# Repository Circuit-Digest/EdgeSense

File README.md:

# EdgeSense: STM32 Edge AI Texture and Gesture Classifier

```
  ███████╗██████╗  ██████╗ ███████╗███████╗███████╗███╗   ██╗███████╗███████╗
  ██╔════╝██╔══██╗██╔════╝ ██╔════╝██╔════╝██╔════╝████╗  ██║██╔════╝██╔════╝
  █████╗  ██║  ██║██║  ███╗█████╗  ███████╗█████╗  ██╔██╗ ██║███████╗█████╗  
  ██╔══╝  ██║  ██║██║   ██║██╔══╝  ╚════██║██╔══╝  ██║╚██╗██║╚════██║██╔══╝  
  ███████╗██████╔╝╚██████╔╝███████╗███████║███████╗██║ ╚████║███████║███████╗
  ╚══════╝╚═════╝  ╚═════╝ ╚══════╝╚══════╝╚══════╝╚═╝  ╚═══╝╚══════╝╚══════╝
```

**EdgeSense** is a compact, high-performance edge artificial intelligence platform that performs on-device 3D gesture recognition, surface/texture classification, static hand posture detection, and optical obscuration sensing. 

Powered by the **STM32H533CEU6** (ARM Cortex-M33 running at 250 MHz) and the **ST VL53L8CH** 8x8 direct Time-of-Flight (dToF) sensor, EdgeSense executes quantized neural networks entirely on-chip in real time with sub-7 ms inference latency.

---

## Key Capabilities

EdgeSense features a runtime multi-model execution engine (`pipeline_manager.c`) allowing dynamic model switching over USB CDC:

1. **3D Gesture Recognition (8x8 ToF, 15 FPS)**:
   - Recognizes dynamic directional swipes: `SWIPE_LEFT`, `SWIPE_RIGHT`, `SWIPE_UP`, `SWIPE_DOWN`, and `IDLE`.
   - Continuous 15-frame sliding window (1.0 s temporal context) with zero gesture-lockout.
   - Physical temporal motion energy guard to eliminate stationary phantom triggers.
   - Inference latency: **~6.8 ms** per inference.

2. **Distance-Invariant Surface Classifier (4x4 CNH, 48 Bins)**:
   - Classifies textures and materials: `HARD_FLOOR` (tile/wood), `CARPET` (subsurface scattering), `SPECULAR` (mirrors/polished metal), and `VOID` (drop-offs/cliffs).
   - Utilizes ST-aligned Cumulative Normalized Histogram (CNH) peak-centered canonical alignment.
   - Inference latency: **~3.2 ms** per inference.

3. **Static Hand Posture Classifier (8x8 Depth + Signal Intensity)**:
   - Identifies static human hand postures: `FLAT_HAND`, `LIKE`, `DISLIKE`, `BREAK_TIME`, `FIST`, and `NONE`.
   - Dual-channel 2D-CNN processing distance geometry and photon reflection intensity simultaneously.
   - Robust to ambient lighting variations and skin tone differences.
   - Inference latency: **~4.1 ms** per inference.

4. **Optical Obscuration & Smoke Detector**:
   - Detects microscopic particles, airborne obscuration, and smoke.
   - Computes multi-zone signal attenuation and ambient light scattering indices in real time.

---

## Hardware Specifications

| Component | Specification |
|---|---|
| **Microcontroller** | STMicroelectronics STM32H533CEUx (ARM Cortex-M33, 250 MHz, TrustZone, FPU, DSP) |
| **On-Chip Memory** | 512 KB Flash ROM, 256 KB SRAM |
| **ToF Sensor** | STMicroelectronics VL53L8CH / VL53LMZ Direct Time-of-Flight |
| **Sensor FoV** | 65° Diagonal Field of View |
| **Spatial Resolution** | 8x8 (64 zones) or 4x4 (16 zones with 48-bin CNH histograms) |
| **Ranging Distance** | 20 mm to 4000 mm |
| **Host Connectivity** | High-Speed USB 2.0 CDC (Virtual COM Port @ 921600 baud) |
| **Communication Bus** | Dedicated Fast-mode Plus (Fm+) 1 MHz I2C bus |
| **Power Supply** | 5V via USB-C or 3.3V external rail |

---

## Repository Structure

```
EdgeSense/
├── Core/                      # STM32H533 HAL drivers, ISRs, and main loop
├── Drivers/                   # CMSIS and STM32H5xx HAL libraries
├── Middlewares/               # ST X-CUBE-AI runtime v10.2.1 & USB Device stack
├── USB_Device/                # USB CDC Virtual COM Port descriptors & handlers
├── VL53LMZ_ULD/               # Ultra-Lite Driver & CNH Histogram Plugin
├── X-CUBE-AI/                 # Edge AI Pipeline Manager & Active Networks
│   └── App/                   # pipeline_manager, model_gesture, model_posture, model_surface, model_smoke
│
├── Models/                    # Pre-trained production ONNX models & datasets
│   ├── gesture_nn_model.onnx  # 5-class 2D-CNN Gesture Classifier
│   ├── posture_nn_model.onnx  # 6-class 2D-CNN Posture Classifier
│   ├── surface_nn_model.onnx  # 4-class 1D-CNN Surface Classifier
│   ├── gesture_dataset.npz    # Default Gesture training dataset
│   ├── posture_dataset.npz    # Default Posture training dataset
│   ├── surface_dataset.npz    # Default Surface training dataset
│   └── Archive/               # Intermediate training iterations
│
├── Tools/                     # Python Studio, GUIs, and deploy automation
│   ├── Studio/                # 4-in-1 EdgeSense Neural Network Studio
│   │   ├── run_nn_studio.bat  # Double-click to launch Studio GUI
│   │   ├── deploy_to_project.bat # Unified model conversion & firmware build
│   │   ├── edgesense_nn_studio.py
│   │   ├── requirements.txt
│   │   └── utils/             # ST-AI helpers and zip importers
│   ├── Visualizer/            # Real-time multi-zone depth viewer
│   ├── Flashing/              # STM32CubeProgrammer CLI flasher (USB DFU & ST-LINK)
│   └── Tests/                 # Automated AT pipeline verification tests
│
├── Hardware/                  # KiCad EDA design files, schematics & BOM
│   ├── Schematics/            # KiCad project, schematics, PCB layout
│   └── Production/            # Gerber ZIP, Pick-and-Place, BOM
│
├── Docs/                      # Technical references & protocol manuals
│   ├── Architecture.md        # System architecture and memory specs
│   └── AT_Command_Manual.md   # Complete AT command serial reference
│
├── EdgeSense.ioc              # STM32CubeMX hardware pinout and clock config
├── STM32H533CEUX_FLASH.ld     # Flash linker script
├── LICENSE                    # GNU General Public License v3.0
└── README.md                  # This documentation
```

---

## Getting Started

### 1. Prerequisites
- **STM32CubeIDE** (v2.2.0 or newer) with GNU Tools for STM32 (ARM GCC 14.3+)
- **STM32Cube.AI Studio (STEDGEAI-CUBEAI)** / **ST Edge AI Core** (`stedgeai`) v10.2.1+
- **Python** 3.10+ (64-bit)
- **ST-LINK V2 / V3** Programmer

### 2. Python Environment Setup
Install the required dependencies for the EdgeSense AI Studio:
```bash
cd Tools/Studio
pip install -r requirements.txt
```

### 3. Launching EdgeSense Studio
Double-click `Tools/Studio/run_nn_studio.bat` or run:
```bash
python Tools/Studio/edgesense_nn_studio.py
```
From the Studio, you can:
- View live 8x8 depth heatmaps and 4x4 CNH pulse shapes.
- Record new training datasets for Gestures, Postures, or Surfaces.
- Train PyTorch neural networks with 1 click.
- Deploy trained models to the project via `deploy_to_project.bat`.

### 4. Building Firmware via Command Line
```bash
make -C Debug all
```
The compiled binary will be located at `Debug/EdgeSense.elf` and `Debug/EdgeSense.bin`.

### 5. Flashing Firmware
Choose your preferred flashing method:
- **USB-C (DFU Mode - No external programmer required)**:
  1. Press and hold `SW2` (BOOT0), press and release `SW1` (RESET), then release `SW2`.
  2. Run:
  ```bash
  Tools/Flashing/flash_firmware_usb.bat
  ```
- **ST-LINK (SWD Mode)**:
  Connect your ST-LINK probe to the J3 header and run:
  ```bash
  Tools/Flashing/flash_firmware.bat
  ```
- **STM32CubeIDE**:
  Open the project in STM32CubeIDE and click **Run** or **Debug**.

---

## Serial Communication & AT Commands

Connect to the USB CDC COM port at **921600 baud, 8-N-1**.

| Command | Action |
|---|---|
| `AT` | Verify connection (returns `OK`) |
| `AT+MODE=?` | List available modes: `(0:GESTURE, 1:SURFACE, 2:POSTURE, 3:SMOKE)` |
| `AT+MODE?` | Query currently active mode |
| `AT+MODE=0` | Switch to 3D Gesture Recognition mode |
| `AT+MODE=1` | Switch to Surface / Texture Classifier mode |
| `AT+MODE=2` | Switch to Hand Posture Classifier mode |
| `AT+MODE=3` | Switch to Optical Smoke / Obscuration mode |
| `AT+STREAM=1` | Enable real-time 8x8 JSON depth streaming |
| `AT+STREAM=0` | Disable streaming |
| `AT+STATUS` | View sensor health, frame counts, and FPS |
| `AT+RESET` | Software system reboot |

---

## License

This project is licensed under the **GNU General Public License v3.0**. See the [LICENSE](LICENSE) file for details.

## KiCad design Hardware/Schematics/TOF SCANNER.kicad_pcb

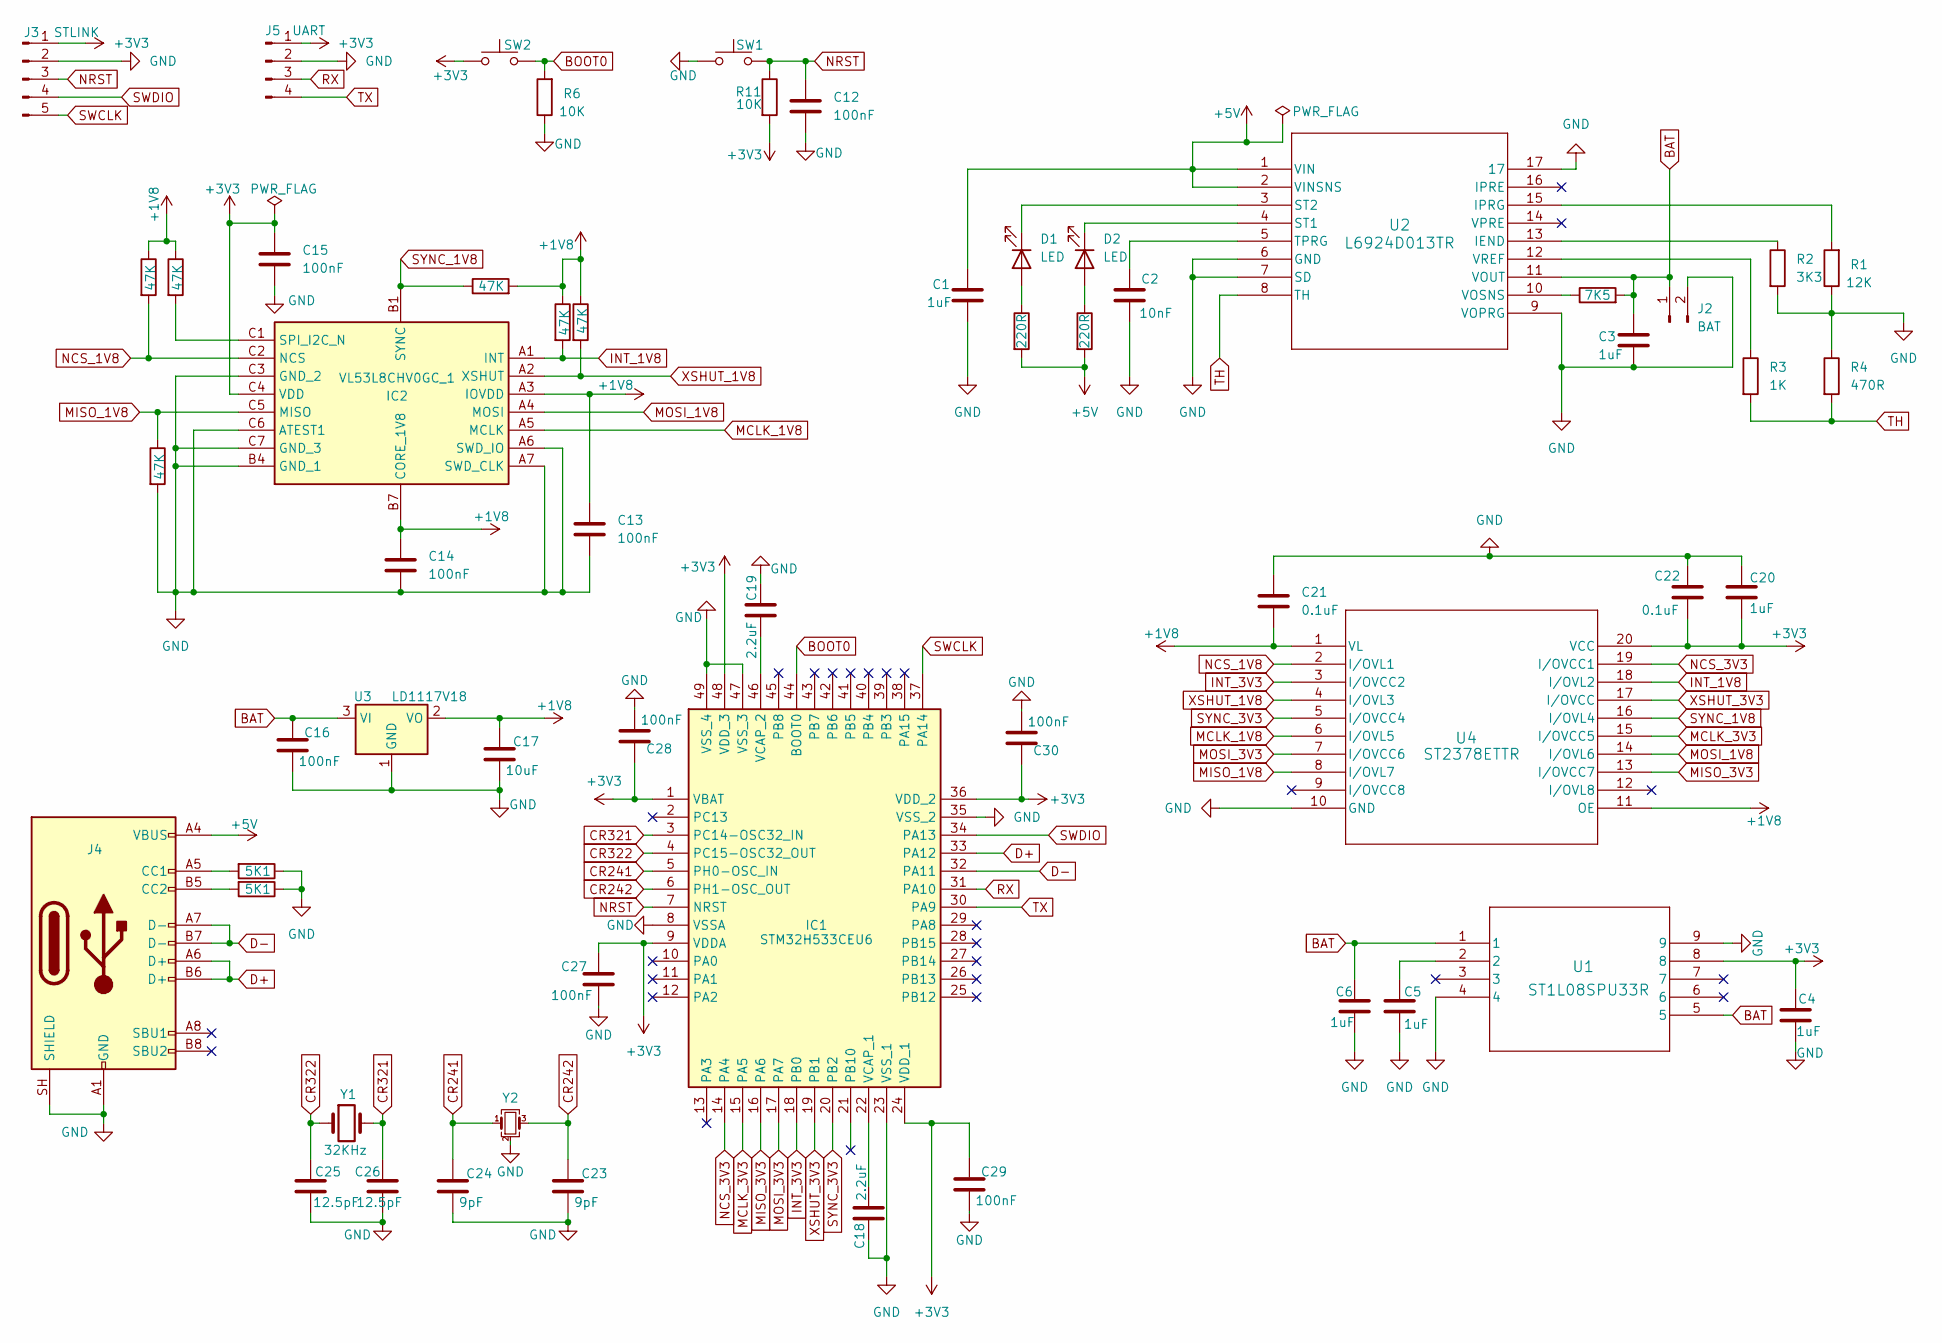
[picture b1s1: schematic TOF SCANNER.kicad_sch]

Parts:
C1, C3, C4, C5, C6, C20: 1uF; C_0603_1608Metric
C2: 10nF; C_0603_1608Metric
C12, C13, C14, C15, C16, C27, C28, C29, C30: 100nF; C_0603_1608Metric
C17: 10uF; C_0603_1608Metric
C18, C19: 2.2uF; C_0603_1608Metric
C21, C22: 0.1uF; C_0603_1608Metric
C23, C24: 9pF; C_0603_1608Metric
C25, C26: 12.5pF; C_0603_1608Metric
D1, D2: LED; LED_0603_1608Metric
IC1: STM32H533CEU6; UFQFPN-48_STM; Mouser Part Number 511-STM32H533CEU6
IC2: VL53L8CHV0GC_1; VL53L8CHV0GC1; Mouser Part Number 511-VL53L8CHV0GC/1
J2: BAT; JST_PH_B2B-PH-K_1x02_P2.00mm_Vertical
J3: STLINK; PinHeader_1x05_P2.54mm_Vertical
J4: USB_C_Receptacle_USB2.0_16P; USB_C_Receptacle_HCTL_HC-TYPE-C-16P-01A
J5: UART; PinHeader_1x04_P2.54mm_Vertical
R1: 12K; R_0603_1608Metric
R2: 3K3; R_0603_1608Metric
R3: 1K; R_0603_1608Metric
R4: 470R; R_0603_1608Metric
R5, R7: 220R; R_0603_1608Metric
R6, R11: 10K; R_0603_1608Metric
R8, R9, R10, R14, R15, R16: 47K; R_0603_1608Metric
R12, R13: 5K1; R_0603_1608Metric
R17: 7K5; R_0603_1608Metric
SW1, SW2: SW_Push; SW_SPST_TS-1088-xR025
U1: ST1L08SPU33R; DFN_SPU33R_STM
U2: L6924D013TR; VFQFPN-16_STM
U3: LD1117V18; SOT-223-3_TabPin2
U4: ST2378ETTR; TSSOP20_4P4X6P5_STM
Y1: 32KHz; Crystal_SMD_3215-2Pin_3.2x1.5mm
Y2: Crystal_GND24_Small; Crystal_SMD_3225-4Pin_3.2x2.5mm

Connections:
+1V8: C13.1, C14.1, C17.1, C21.2, IC2.A3 (IOVDD), IC2.B7 (CORE_1V8), R8.1, R9.2, R10.1, R14.1, R15.1, U3.2 (VO), U4.1 (VL), U4.11 (OE)
+3V3: C4.1, C15.1, C20.2, C22.2, C27.1, C28.1, C29.1, C30.1, IC1.1 (VBAT), IC1.9 (VDDA), IC1.24 (VDD_1), IC1.36 (VDD_2), IC1.48 (VDD_3), IC2.C4 (VDD), J3.1, J5.1, R11.2, SW2.1, U1.8, U4.20 (VCC)
+5V: C1.1, J4.A4 (VBUS), J4.A9 (VBUS), J4.B4 (VBUS), J4.B9 (VBUS), R5.2, R7.2, U2.1 (VIN), U2.2 (VINSNS)
BAT: C3.1, C6.1, C16.1, J2.1, R17.2, U1.1, U1.5, U2.11 (VOUT), U3.3 (VI)
BOOT0: IC1.44 (BOOT0), R6.2, SW2.2
CR241: C24.1, IC1.5 (PH0-OSC_IN), Y2.1
CR242: C23.1, IC1.6 (PH1-OSC_OUT), Y2.3
CR321: C26.1, IC1.3 (PC14-OSC32_IN), Y1.2
CR322: C25.1, IC1.4 (PC15-OSC32_OUT), Y1.1
D+: IC1.33 (PA12), J4.A6 (D+), J4.B6 (D+)
D-: IC1.32 (PA11), J4.A7 (D-), J4.B7 (D-)
GND: C1.2, C2.2, C3.2, C4.2, C5.2, C6.2, C12.2, C13.2, C14.2, C15.2, C16.2, C17.2, C18.1, C19.2, C20.1, C21.1, C22.1, C23.2, C24.2, C25.2, C26.2, C27.2, C28.2, C29.2, C30.2, IC1.8 (VSSA), IC1.23 (VSS_1), IC1.35 (VSS_2), IC1.47 (VSS_3), IC1.49 (VSS_4), IC2.A6 (SWD_IO), IC2.A7 (SWD_CLK), IC2.B4 (GND_1), IC2.C3 (GND_2), IC2.C6 (ATEST1), IC2.C7 (GND_3), J2.2, J3.2, J4.A1 (GND), J4.A12 (GND), J4.B1 (GND), J4.B12 (GND), J4.SH (SHIELD), J5.2, R1.1, R2.2, R4.1, R6.1, R12.1, R13.1, R16.2, SW1.1, U1.4, U1.9, U2.6 (GND), U2.7 (SD), U2.9 (VOPRG), U2.17, U3.1 (GND), U4.10 (GND), Y2.2 (G), Y2.4 (G)
INT_1V8: IC2.A1 (INT), R8.2, U4.18 (I/OVL2)
INT_3V3: IC1.18 (PB0), U4.3 (I/OVCC2)
MCLK_1V8: IC2.A5 (MCLK), U4.6 (I/OVL5)
MCLK_3V3: IC1.15 (PA5), U4.15 (I/OVCC5)
MISO_1V8: IC2.C5 (MISO), R16.1, U4.8 (I/OVL7)
MISO_3V3: IC1.16 (PA6), U4.13 (I/OVCC7)
MOSI_1V8: IC2.A4 (MOSI), U4.14 (I/OVL6)
MOSI_3V3: IC1.17 (PA7), U4.7 (I/OVCC6)
NCS_1V8: IC2.C2 (NCS), R15.2, U4.2 (I/OVL1)
NCS_3V3: IC1.14 (PA4), U4.19 (I/OVCC1)
NRST: C12.1, IC1.7 (NRST), J3.3, R11.1, SW1.2
unnamed: C5.1, U1.2
unnamed: D1.2 (A), R7.1
unnamed: D1.1 (K), U2.3 (ST2)
unnamed: D2.2 (A), R5.1
unnamed: D2.1 (K), U2.4 (ST1)
unnamed: C18.2, IC1.22 (VCAP_1)
unnamed: C19.1, IC1.46 (VCAP_2)
unnamed: IC2.C1 (SPI_I2C_N), R14.2
unnamed: J4.A5 (CC1), R12.2
unnamed: J4.B5 (CC2), R13.2
unnamed: R2.1, U2.13 (IEND)
unnamed: R1.2, U2.15 (IPRG)
unnamed: C2.1, U2.5 (TPRG)
unnamed: R17.1, U2.10 (VOSNS)
unnamed: R3.1, U2.12 (VREF)
RX: IC1.31 (PA10), J5.3
SWCLK: IC1.37 (PA14), J3.5
SWDIO: IC1.34 (PA13), J3.4
SYNC_1V8: IC2.B1 (SYNC), R9.1, U4.16 (I/OVL4)
SYNC_3V3: IC1.20 (PB2), U4.5 (I/OVCC4)
TH: R3.2, R4.2, U2.8 (TH)
TX: IC1.30 (PA9), J5.4
XSHUT_1V8: IC2.A2 (XSHUT), R10.2, U4.4 (I/OVL3)
XSHUT_3V3: IC1.19 (PB1), U4.17 (I/OVCC)

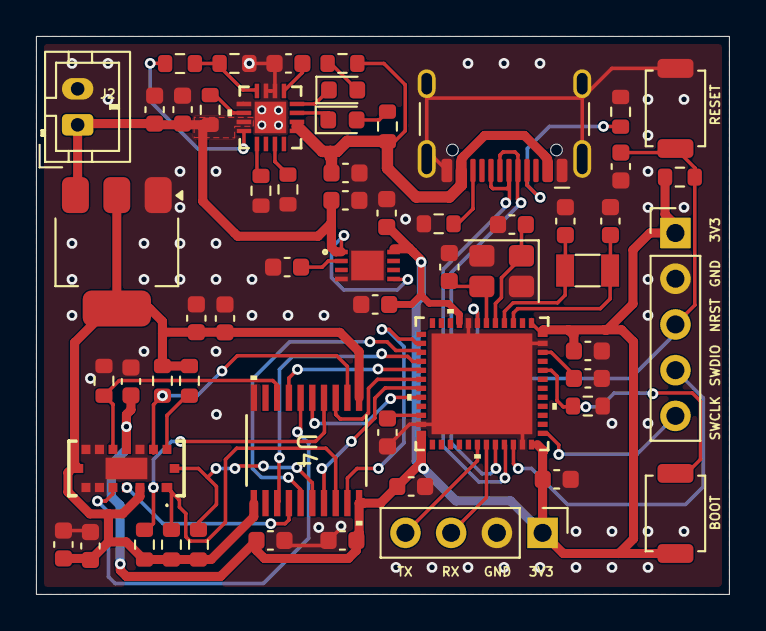
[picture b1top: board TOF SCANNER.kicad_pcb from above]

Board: 2 copper layers, 38.5 x 31.0 mm, 58 parts (0 on the bottom side), 47 nets.

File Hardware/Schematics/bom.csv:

Designator,Footprint,Quantity,Manufacturer part number,LCSC Part #
BAT,JST_PH_B2B-PH-K_1x02_P2.00mm_Vertical,1,BAT,
"C1, C20, C3, C4, C5, C6",603,6,1uF,
"C10, C12, C13, C14, C15, C16, C8, C9",603,8,100nF,
"C17, C23, C24",603,3,10uF,
"C18, C19",603,2,2.2uF,
C2,603,1,10nF,
"C21, C22",603,2,0.1uF,
"C25, C26",603,2,9pF,
"D1, D2",603,2,LED,
IC1,UFQFPN-48_STM,1,STM32H533CEU6,
IC2,VL53L8CHV0GC1,1,VL53L8CHV0GC_1,
J3,PinHeader_1x05_P2.54mm_Vertical,1,STLINK,
J4,USB_C_Receptacle_HCTL_HC-TYPE-C-16P-01A,1,USB_C_Receptacle_USB2.0_16P,
J5,PinHeader_1x04_P2.54mm_Vertical,1,UART,
R1,603,1,12K,
"R10, R14, R15, R16, R8, R9",603,6,47K,
"R11, R6",603,2,10K,
"R12, R13",603,2,5K1,
R17_2,603,1,7K5,
R17,603,1,7500R,
R2,603,1,3K3,
R3,603,1,1K,
R4,603,1,470R,
"R5, R7",603,2,220R,
"SW1, SW2",SW_SPST_TS-1088-xR025,2,SW_Push,
U1,DFN_SPU33R_STM,1,ST1L08SPU33R,
U2,VFQFPN-16_STM,1,L6924D013TR,
U3,SOT-223-3_TabPin2,1,LD1117V18,
U4,TSSOP20_4P4X6P5_STM,1,ST2378ETTR,
Y1,Crystal_SMD_3215-2Pin_3.2x1.5mm,1,32KHz,
Y2,XTAL_ABM8-24.000MHZ-D2Y-T,1,24MHz,

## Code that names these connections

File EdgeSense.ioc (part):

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Mcu.Name=STM32H533CEUx
Mcu.Package=UFQFPN48
Mcu.UserName=STM32H533CEUx
PA10.Mode=Asynchronous
PA10.Signal=USART1_RX
PA11.Mode=Device
PA11.Signal=USB_DM
PA12.Mode=Device
PA12.Signal=USB_DP
PA13(JTMS/SWDIO).Mode=Serial_Wire
PA13(JTMS/SWDIO).Signal=DEBUG_JTMS-SWDIO
PA14(JTCK/SWCLK).Mode=Serial_Wire
PA14(JTCK/SWCLK).Signal=DEBUG_JTCK-SWCLK
PA4.GPIOParameters=PinState,GPIO_PuPd,GPIO_Label
PA4.GPIO_Label=VL_NCS
PA4.GPIO_PuPd=GPIO_PULLUP
PA4.PinState=GPIO_PIN_SET
PA4.Signal=GPIO_Output
PA5.Mode=Full_Duplex_Master
PA5.Signal=SPI1_SCK
PA6.Mode=Full_Duplex_Master
PA6.Signal=SPI1_MISO
PA7.Mode=Full_Duplex_Master
PA7.Signal=SPI1_MOSI
PA9.Mode=Asynchronous
PA9.Signal=USART1_TX
PB0.GPIOParameters=GPIO_PuPd,GPIO_Label
PB0.GPIO_Label=VL_INT
PB0.GPIO_PuPd=GPIO_PULLUP
PB0.Signal=GPIO_Input
PB1.GPIOParameters=PinState,GPIO_Label
PB1.GPIO_Label=VL_XSHUT
PB1.PinState=GPIO_PIN_RESET
PB1.Signal=GPIO_Output
PB2.GPIOParameters=GPIO_Label
PB2.GPIO_Label=VL_SYNC
PB2.Signal=GPIO_Output
PC14-OSC32_IN(OSC32_IN).Mode=LSE-External-Oscillator
PC14-OSC32_IN(OSC32_IN).Signal=RCC_OSC32_IN
PC15-OSC32_OUT(OSC32_OUT).Mode=LSE-External-Oscillator
PC15-OSC32_OUT(OSC32_OUT).Signal=RCC_OSC32_OUT
PH0-OSC_IN(PH0).Mode=HSE-External-Oscillator
PH0-OSC_IN(PH0).Signal=RCC_OSC_IN
PH1-OSC_OUT(PH1).Mode=HSE-External-Oscillator
PH1-OSC_OUT(PH1).Signal=RCC_OSC_OUT
RCC.HSE_VALUE=24000000
RCC.SYSCLKFreq_VALUE=240000000
RCC.SYSCLKSource=RCC_SYSCLKSOURCE_PLLCLK
board=custom

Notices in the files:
README.md:
License: GPL v3
